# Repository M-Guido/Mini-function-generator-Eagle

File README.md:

# Mini Function Generator — PCB Project
 
**Author:** Mikołaj Gałązka   
**Tool:** Autodesk EAGLE  

---

## Overview

A compact sequential signal generator PCB designed in Autodesk EAGLE. The circuit uses a tunable **NE555** timer as a clock source driving a **CD4052** analog multiplexer, with **BC547** NPN transistors acting as output current amplifiers. The output frequency is continuously adjustable via a trimmer potentiometer.

The board is suitable for controlling cyclic processes, LED chaser effects, or general low-frequency signal generation tasks on an electronics workbench.

---

## How It Works

1. The **NE555** (IC1) operates in astable mode, generating a square wave clock signal at a frequency set by the RC network and trimmer potentiometer (R14).
2. The **CD4052** dual 4-channel analog multiplexer (IC2) receives the clock pulses and sequentially switches between outputs, creating a traveling wave effect.
3. Two **BC547** NPN transistors (T1, T2) buffer the outputs to safely drive real loads.
4. A **1N4004** diode (D1) provides reverse-polarity protection on the power input.

---

## Key Components

| Part | Value / Type | Description |
|------|-------------|-------------|
| IC1 | NE555 (LINEAR_555N) | Astable timer / clock generator |
| IC2 | CD4052 (4052N) | Dual 4-channel analog multiplexer |
| T1, T2 | BC547 | NPN transistors — output drivers |
| D1 | 1N4004 | Reverse polarity protection diode |
| R14 | 47kΩ trimmer | Frequency adjustment potentiometer |
| C10 | 100µF / 25V | Power supply filter capacitor |
| X1, X2 | WAGO 237 | 2-pin screw terminal connectors |
| JP1 | 2-pin jumper | Configuration jumper |

## PCB Details

- **Package standard:** SMD resistors/capacitors in 1206, ICs in DIP packages
- **Custom library:** `GałązkaUkład.lbr` — standard footprints modified with enlarged solder pads for easier hand soldering
- **Supply voltage:** +5V DC
- **Board files:** schematic (`.sch`) and board layout (`.brd`) exported from EAGLE

---

## Repository Contents

```
├── GałązkaUkład.sch       # EAGLE schematic
├── GałązkaUkład.brd       # EAGLE board layout
├── GałązkaUkład.lbr       # Custom component library
├── .gpi and .pho gerbers/               # Gerber files ready for fabrication drills and pcb schema
└── README.md
```

---

## Commissioning & Measurement Plan

Before powering up, perform a visual inspection of solder joints and component polarity, and run a short-circuit test on the power connector.

**Test equipment needed:**
- Lab power supply (with current limiting set ~200mA)
- Digital multimeter (ammeter + voltmeter mode)
- 2-channel digital oscilloscope

**Parameters to measure:**

| Parameter | Method |
|-----------|--------|
| Supply current draw | Ammeter in series with V+ |
| NE555 output frequency & duty cycle | Oscilloscope on IC1 pin 3 |
| NE555 capacitor charging waveform | Oscilloscope on IC1 pin 2/6 |
| CD4052 output voltage levels | Voltmeter on IC2 outputs |
| Transistor operating points (V_CE, I_C) | Multimeter |

Adjust R14 (trimmer) across its full range and record the min/max output frequency of the NE555.

---

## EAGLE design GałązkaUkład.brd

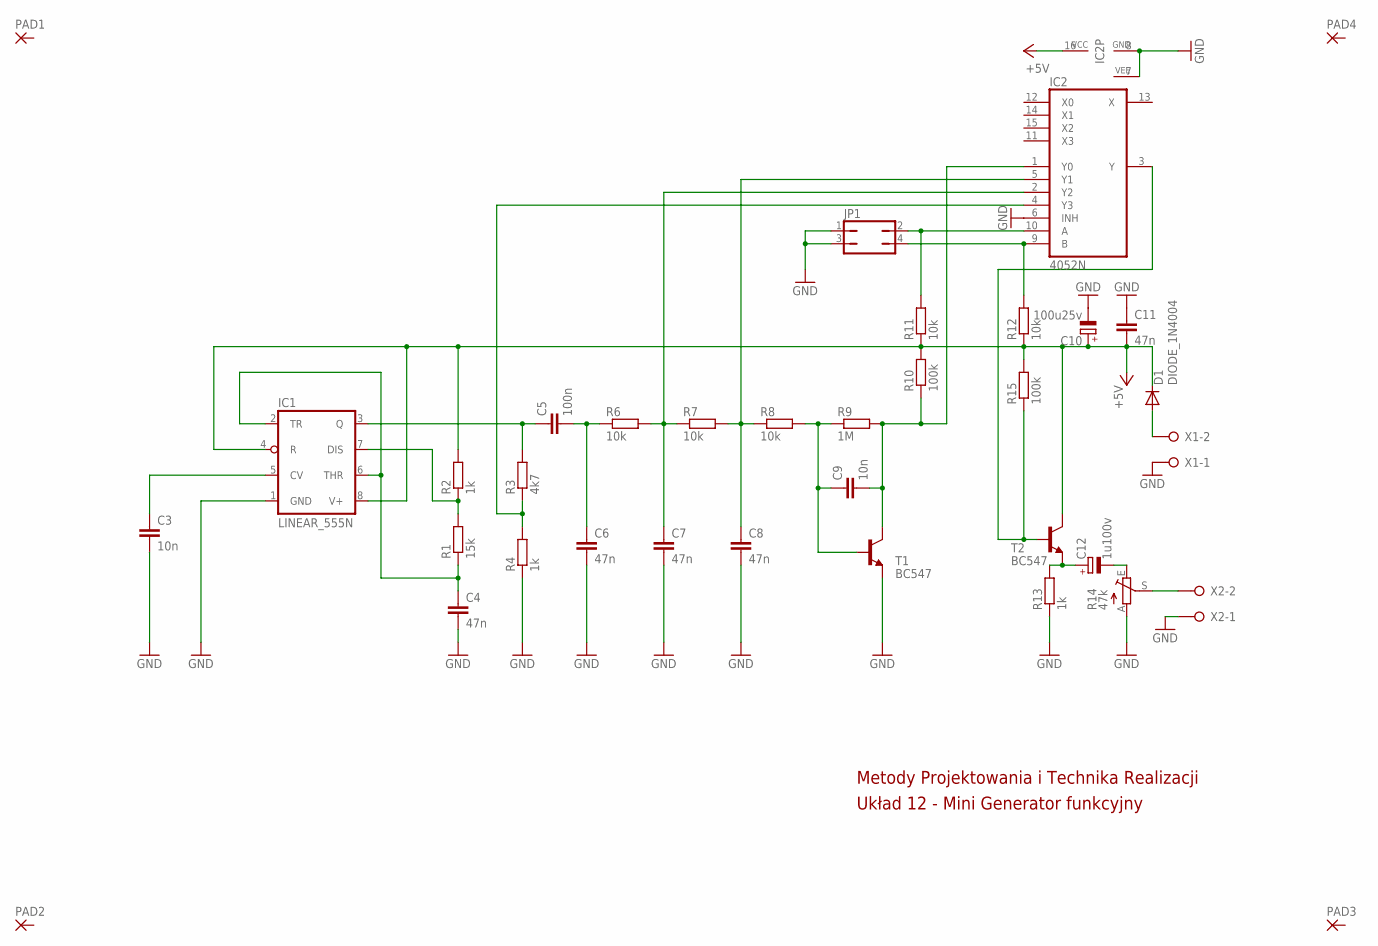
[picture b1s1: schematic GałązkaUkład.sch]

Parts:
C3, C9: 10n; C1206
C4, C6, C7, C8, C11: 47n; C1206
C5: 100n; C1206
C10: 100u25v; RCL_E2,5-6
C12: 1u100v; E2-5
D1: DIODE_1N4004; DIODE_DO41-10
IC1: LINEAR_555N; LINEAR_DIL08
IC2: 4052N; DIL16
JP1: JUMPER_JP2Q
PAD1, PAD2, PAD3, PAD4: 2,54/1,1
R1: 15k; R1206
R2, R4, R13: 1k; R1206
R3: 4k7; R1206
R6, R7, R8, R11, R12: 10k; R1206
R9: 1M; R1206
R10, R15: 100k; R1206
R14: 47k; POT_CA6V
T1, T2: BC547; TO92
X1, X2: CON-WAGO-508_W237-02P; CON-WAGO-508_W237-132

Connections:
+5V: C10.+, C11.2, D1.C, IC1.4 (R), IC1.8 (V+), IC2.16 (VCC), R2.2, R10.2, R11.1, R12.1, R15.2, T2.3 (C)
C9: C9.2, IC2.1 (Y0), R9.2, R10.1, T1.3 (C)
GND: C3.2, C4.2, C6.2, C7.2, C8.2, C10.-, C11.1, IC1.1 (GND), IC2.6 (INH), IC2.7 (VEE), IC2.8 (GND), JP1.1, JP1.3, R4.1, R13.1, R14.A (1), T1.1 (E), X1.1, X2.1
unnamed: C5.2, C6.1, R6.1
unnamed: C7.1, IC2.2 (Y2), R6.2, R7.1
unnamed: C8.1, IC2.5 (Y1), R7.2, R8.1
unnamed: C9.1, R8.2, R9.1, T1.2 (B)
unnamed: IC2.10 (A), JP1.2, R11.2
unnamed: C12.-, R14.E (2)
unnamed: R14.S (3), X2.2
unnamed: IC2.9 (B), JP1.4, R12.2
unnamed: C5.1, IC1.3 (Q), R3.2
unnamed: C4.1, IC1.2 (TR), IC1.6 (THR), R1.1
unnamed: IC1.7 (DIS), R1.2, R2.1
unnamed: C3.1, IC1.5 (CV)
unnamed: IC2.3 (Y), R15.1, T2.2 (B)
unnamed: IC2.4 (Y3), R3.1, R4.2
unnamed: C12.+, R13.2, T2.1 (E)
unnamed: D1.A, X1.2

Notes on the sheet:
Układ 12 - Mini Generator funkcyjny
Metody Projektowania i Technika Realizacji

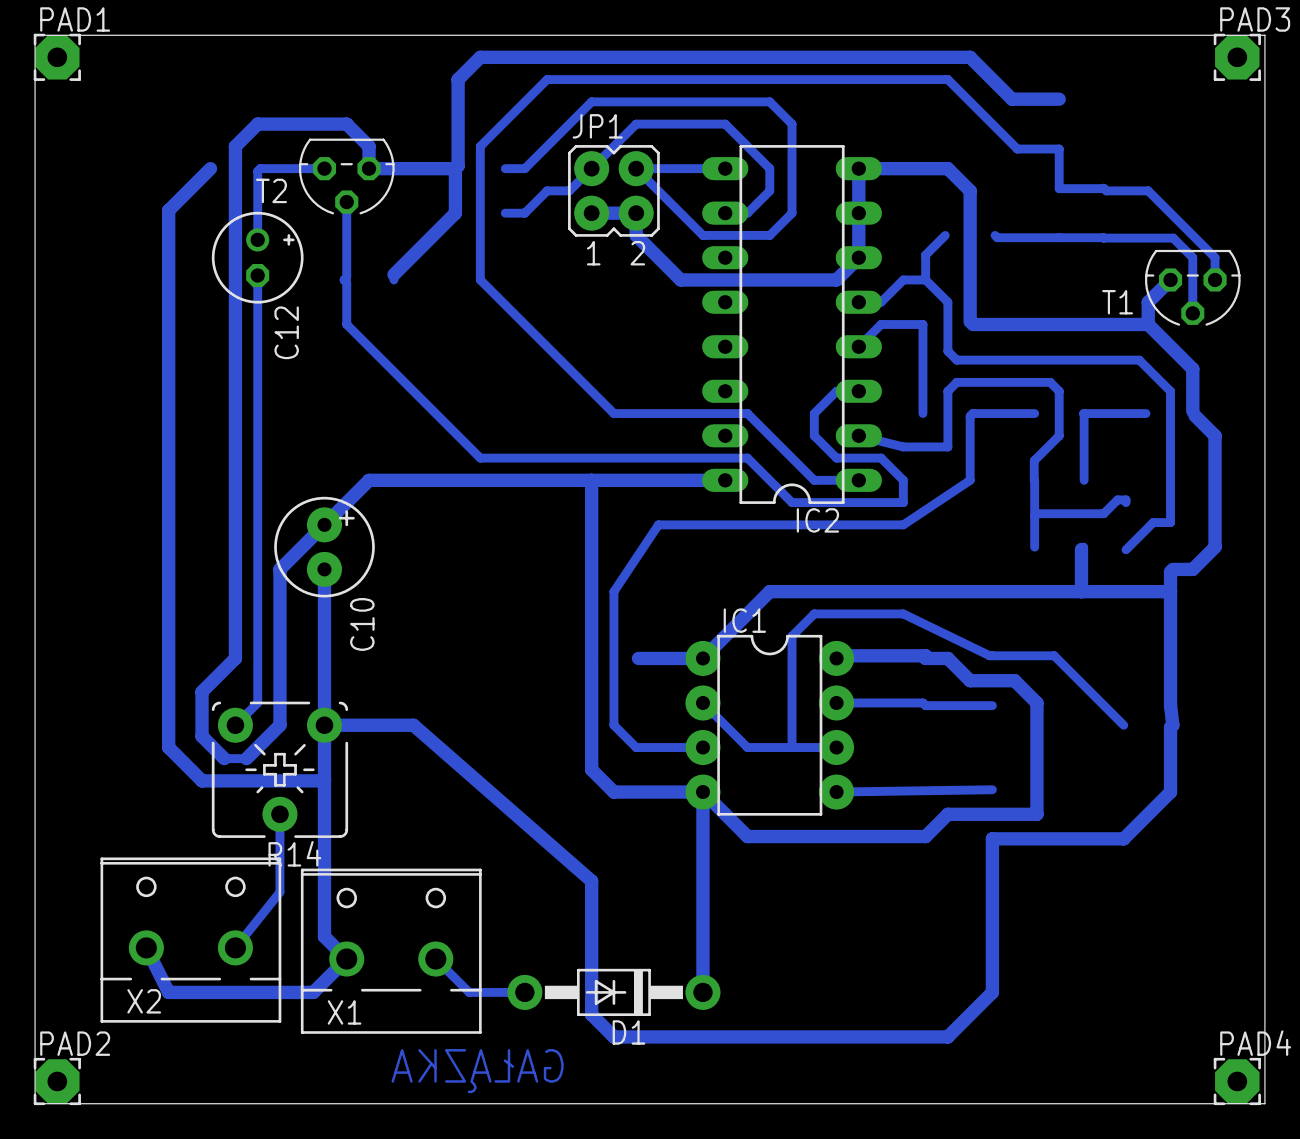
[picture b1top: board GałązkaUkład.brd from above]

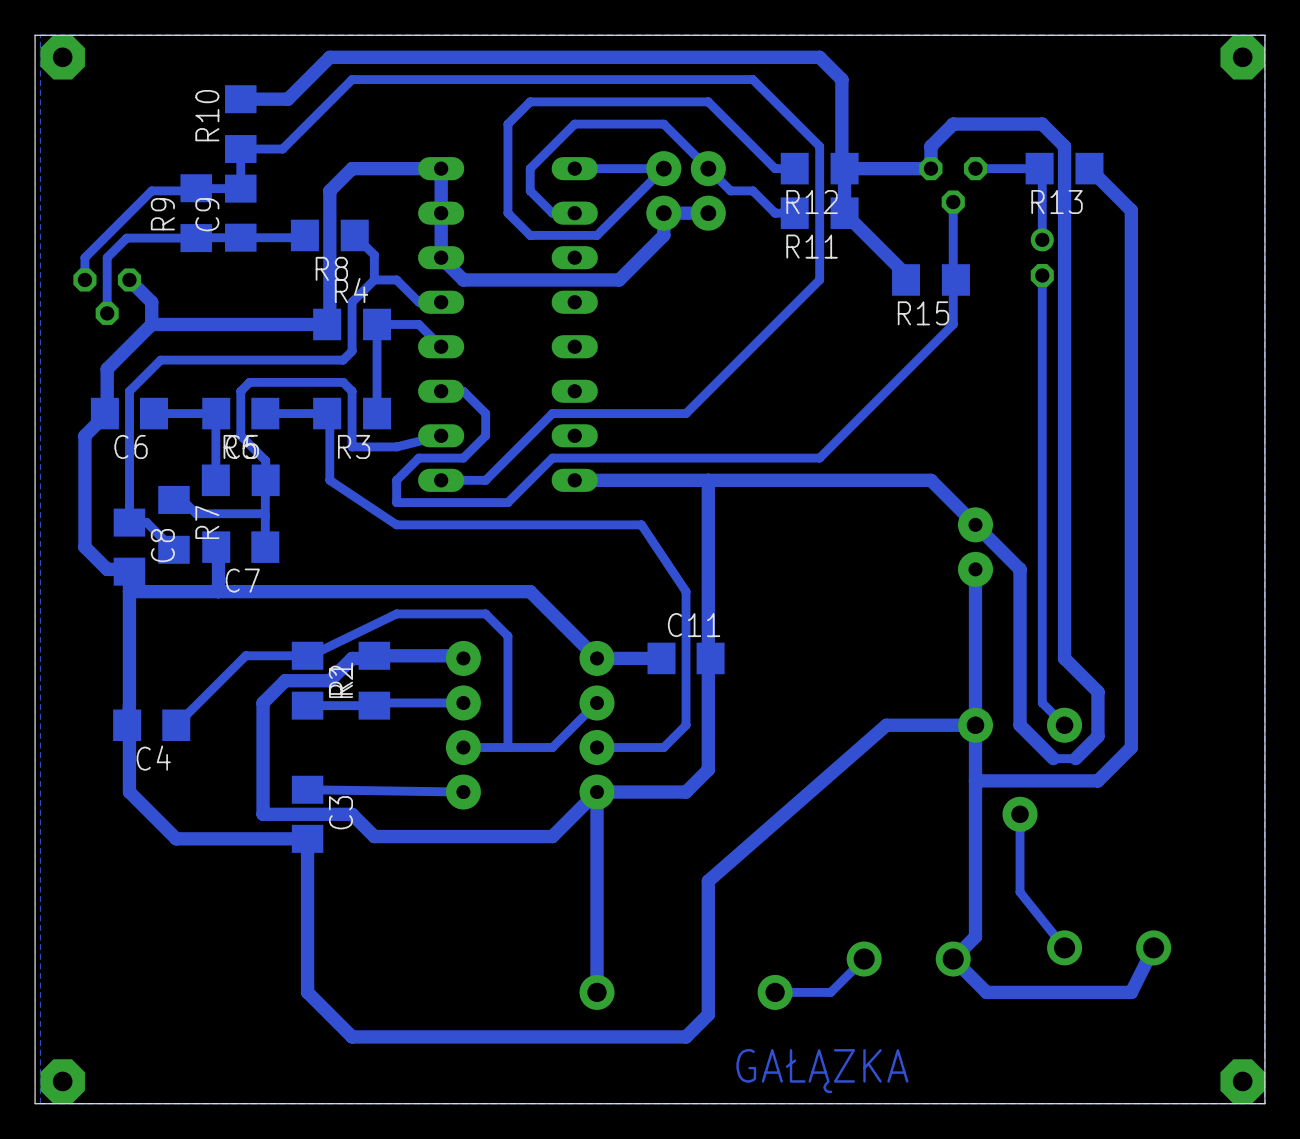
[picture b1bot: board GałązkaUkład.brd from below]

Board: 2 copper layers, 70.2 x 61.0 mm, 36 parts (21 on the bottom side), 19 nets.

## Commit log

2026-04-30 Initial commit - Mini Function Generator PCB
